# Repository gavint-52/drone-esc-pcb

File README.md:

# Drone ESC PCB

## Overview
A custom electronic speed controller (ESC) PCB designed for brushless DC motor applications.

## Design Objectives
- Design a three-phase MOSFET power stage.
- Integrate a DRV8320 gate driver.
- Use an STM32 microcontroller for control.
- Design power distribution for a 6S LiPo battery system.

## Hardware Components
- **Microcontroller:** STM32 (exact part number to be added)
- **Gate driver:** DRV8320
- **Power MOSFETs:** TI CSD18532NQ5B
- **Design software:** KiCad

## My Contributions
- Schematic design and component selection
- Gate-driver and MOSFET circuit design
- PCB component placement and routing
- Power and ground layout considerations

## Project Status
At fabrication stage of development.  

## Images
PCB renders and schematic screenshots will be added here.

## Future Work
- Complete PCB layout and design-rule checks
- Prepare fabrication files
- Assemble and test the board# drone-esc-pcb
Custom three-phase drone ESC PCB design using KiCad, an STM32 microcontroller, and a DRV8320 gate driver.

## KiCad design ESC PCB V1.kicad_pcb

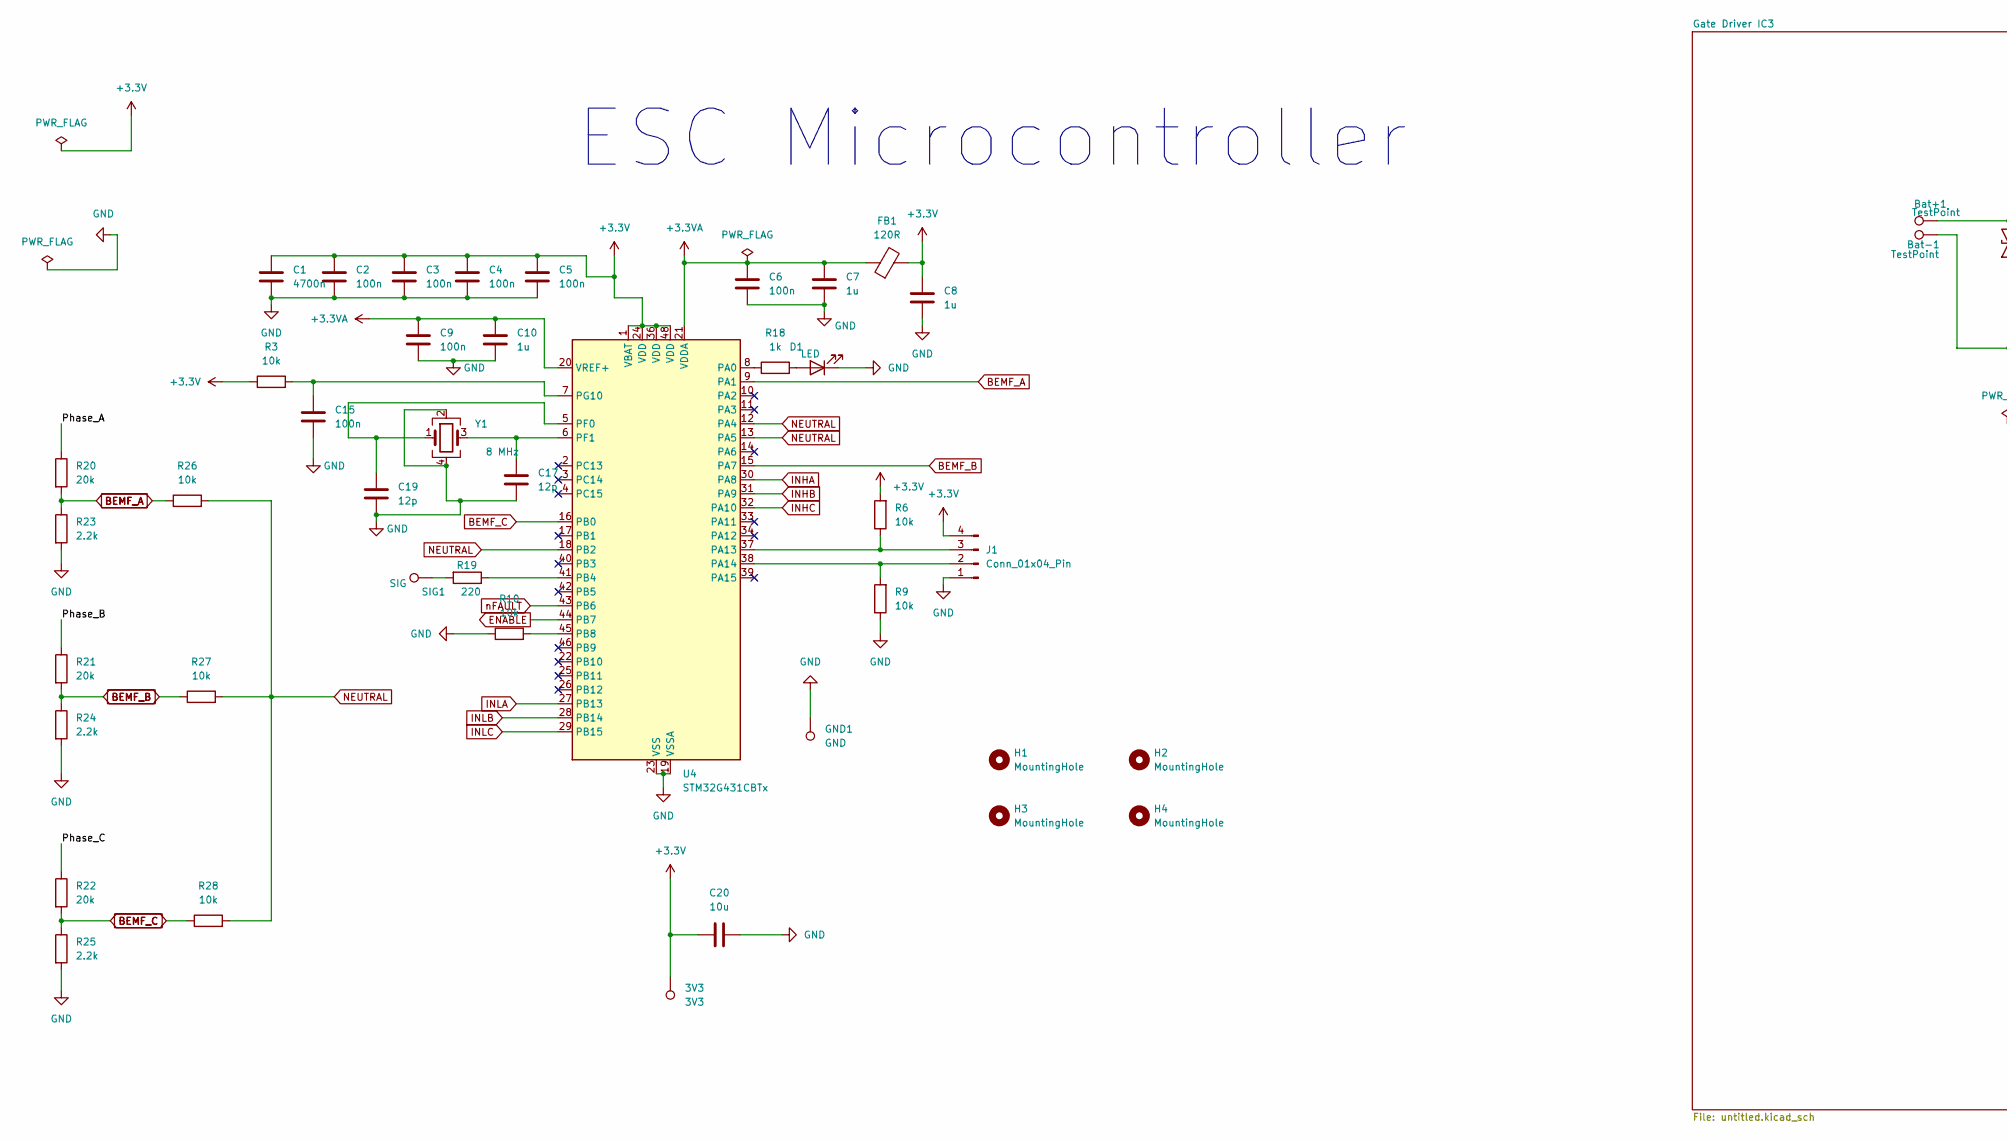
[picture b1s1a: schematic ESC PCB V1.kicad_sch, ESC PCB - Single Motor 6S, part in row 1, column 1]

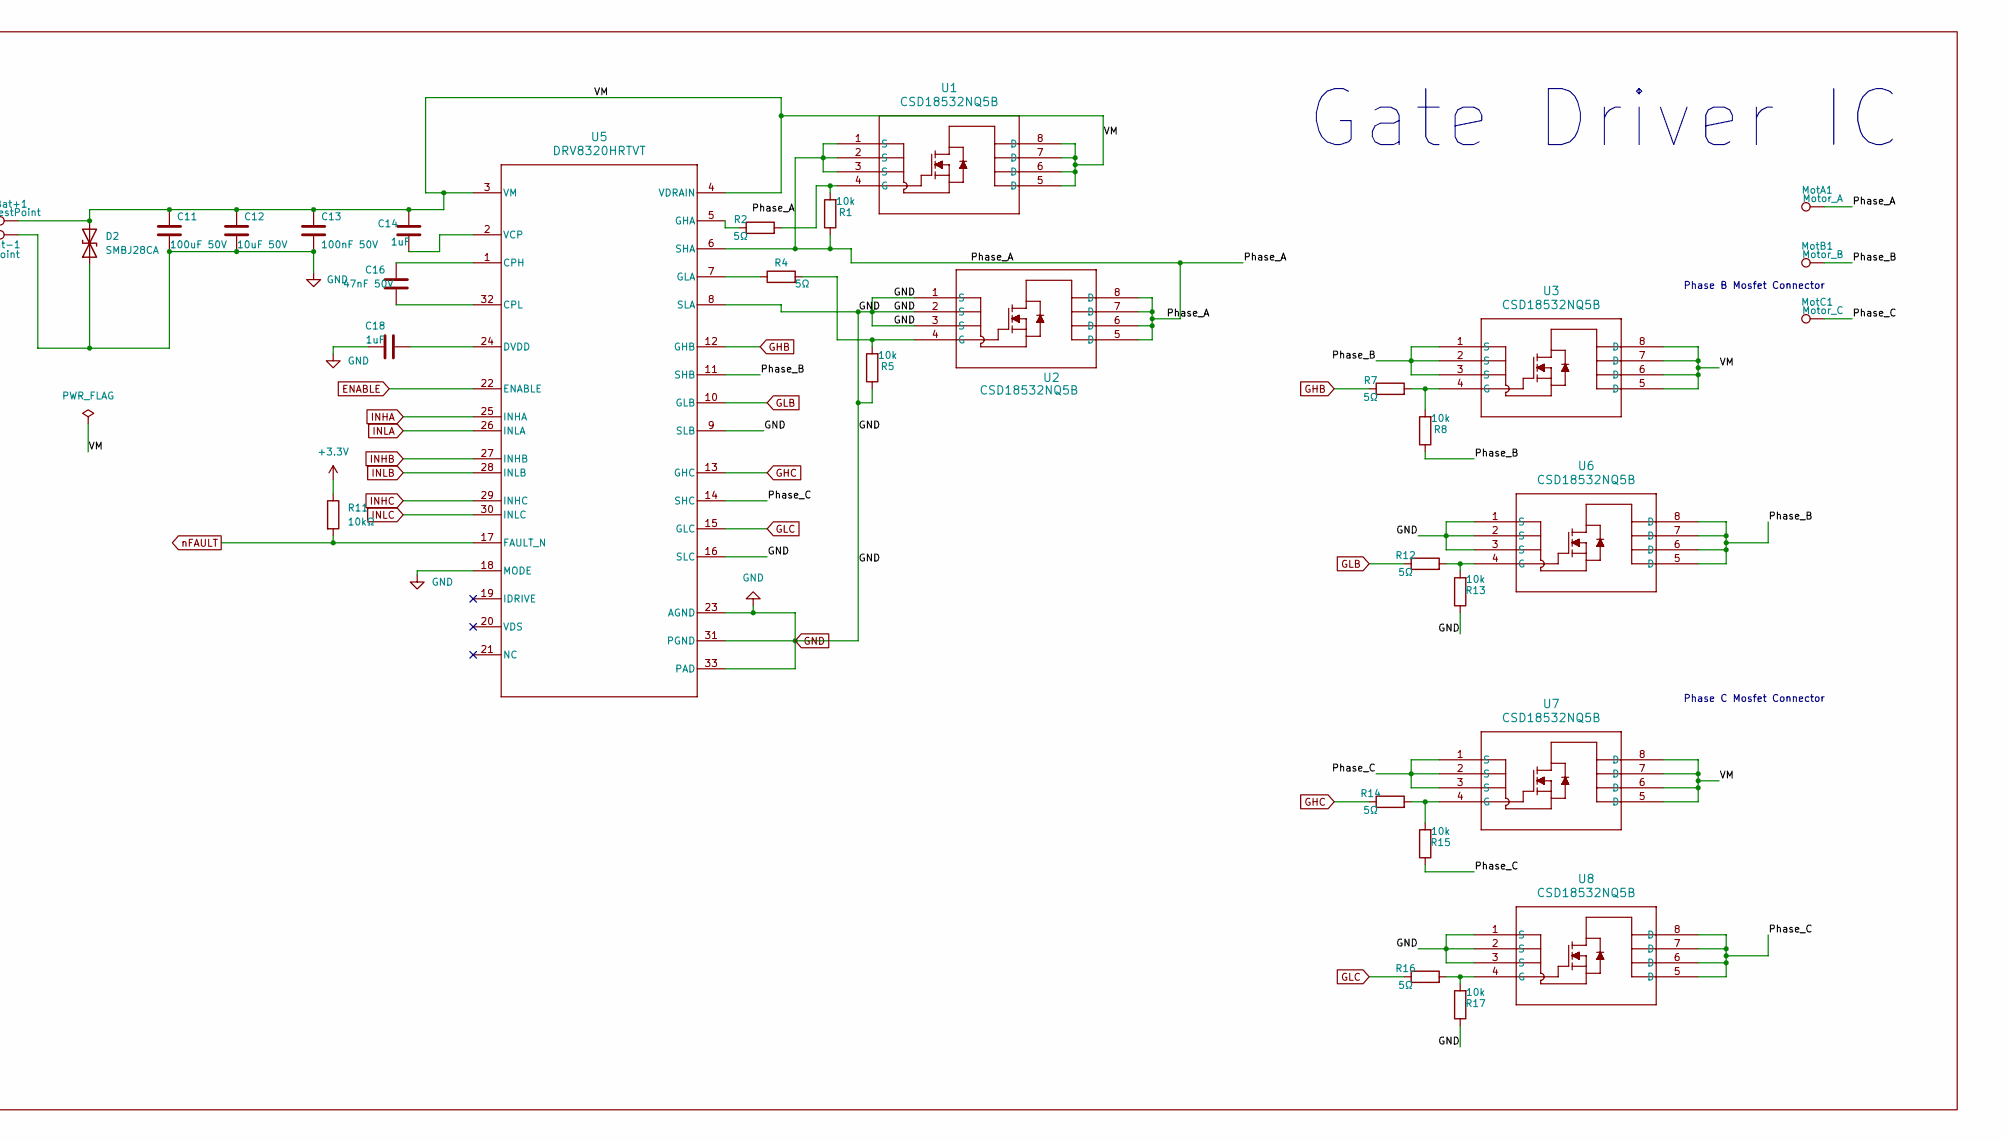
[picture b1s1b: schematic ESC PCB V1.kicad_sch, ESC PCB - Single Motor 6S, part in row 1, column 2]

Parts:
3V3: 3V3; SolderWirePad_1x01_SMD_2x4mm
Bat+1: TestPoint; SolderWirePad_1x01_SMD_5x10mm
Bat-1: TestPoint; SolderWirePad_1x01_SMD_5x10mm
C1: 4700n; C_0603_1608Metric
C2, C3, C4, C5, C6, C9, C15: 100n; C_0603_1608Metric
C7, C8, C10: 1u; C_0603_1608Metric
C11: 100uF 50V; CP_Elec_10x10.5
C12: 10uF 50V; C_1210_3225Metric
C13: 100nF 50V; C_0603_1608Metric
C14, C18: 1uF; C_0603_1608Metric
C16: 47nF 50V; C_0603_1608Metric
C17, C19: 12p; C_0603_1608Metric
C20: 10u; C_0603_1608Metric
D1: LED; LED_0603_1608Metric
D2: SMBJ28CA; SMBJSeries_LTF
FB1: 120R; L_0603_1608Metric
GND1: GND; SolderWirePad_1x01_SMD_2x4mm
H1, H2, H3, H4: MountingHole; MountingHole_3.2mm_M3
J1: Conn_01x04_Pin; PinSocket_1x04_P1.00mm_Vertical
MotA1: Motor_A; SolderWirePad_1x01_SMD_5x10mm
MotB1: Motor_B; SolderWirePad_1x01_SMD_5x10mm
MotC1: Motor_C; SolderWirePad_1x01_SMD_5x10mm
R1, R5, R8, R13, R15, R17: 10k; R_0805_2012Metric
R2, R4, R7, R12, R14, R16: 5Ω; R_0805_2012Metric
R3, R6, R9, R10, R26, R27, R28: 10k; R_0603_1608Metric
R11: 10kΩ; R_0603_1608Metric
R18: 1k; R_0603_1608Metric
R19: 220; R_0603_1608Metric
R20, R21, R22: 20k; R_0603_1608Metric
R23, R24, R25: 2.2k; R_0603_1608Metric
SIG1: SIG; SolderWirePad_1x01_SMD_2x4mm
U1, U2, U3, U6, U7, U8: CSD18532NQ5B; DNK8_TEX
U4: STM32G431CBTx; LQFP-48_7x7mm_P0.5mm
U5: DRV8320HRTVT; RTV0032E
Y1: 8 MHz; Crystal_SMD_3225-4Pin_3.2x2.5mm

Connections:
+3.3V: 3V3.1, C1.1, C2.1, C3.1, C4.1, C5.1, C8.1, C20.1, FB1.2, J1.4, R3.1, R6.2, R11.1, U4.1 (VBAT), U4.24 (VDD), U4.36 (VDD), U4.48 (VDD)
+3.3VA: C6.1, C7.1, C9.1, C10.1, FB1.1, U4.20 (VREF+), U4.21 (VDDA)
/Phase_A: MotA1.1, R1.1, R20.1, U1.1 (S), U1.2 (S), U1.3 (S), U2.5 (D), U2.6 (D), U2.7 (D), U2.8 (D), U5.6 (SHA)
/Phase_B: MotB1.1, R8.1, R21.1, U3.1 (S), U3.2 (S), U3.3 (S), U5.11 (SHB), U6.5 (D), U6.6 (D), U6.7 (D), U6.8 (D)
/Phase_C: MotC1.1, R15.1, R22.1, U5.14 (SHC), U7.1 (S), U7.2 (S), U7.3 (S), U8.5 (D), U8.6 (D), U8.7 (D), U8.8 (D)
/VM: Bat+1.1, C11.1, C12.1, C13.1, C14.2, D2.2 (A2), U1.5 (D), U1.6 (D), U1.7 (D), U1.8 (D), U3.5 (D), U3.6 (D), U3.7 (D), U3.8 (D), U5.3 (VM), U5.4 (VDRAIN), U7.5 (D), U7.6 (D), U7.7 (D), U7.8 (D)
BEMF_A: R20.2, R23.1, R26.1, U4.9 (PA1)
BEMF_B: R21.2, R24.1, R27.1, U4.15 (PA7)
BEMF_C: R22.2, R25.1, R28.1, U4.16 (PB0)
ENABLE: U4.44 (PB7), U5.22 (ENABLE)
GHB: R7.1, U5.12 (GHB)
GHC: R14.1, U5.13 (GHC)
GLB: R12.1, U5.10 (GLB)
GLC: R16.1, U5.15 (GLC)
GND: Bat-1.1, C1.2, C2.2, C3.2, C4.2, C5.2, C6.2, C7.2, C8.2, C9.2, C10.2, C11.2, C12.2, C13.2, C15.2, C17.2, C18.1, C19.2, C20.2, D1.1 (K), D2.1 (A1), GND1.1, J1.1, R5.1, R9.1, R10.1, R13.1, R17.1, R23.2, R24.2, R25.2, U2.1 (S), U2.2 (S), U2.3 (S), U4.19 (VSSA), U4.23 (VSS), U4.35 (VSS), U4.47 (VSS), U5.8 (SLA), U5.9 (SLB), U5.16 (SLC), U5.18 (MODE), U5.23 (AGND), U5.31 (PGND), U5.33 (PAD), U6.1 (S), U6.2 (S), U6.3 (S), U8.1 (S), U8.2 (S), U8.3 (S), Y1.2, Y1.4
INHA: U4.30 (PA8), U5.25 (INHA)
INHB: U4.31 (PA9), U5.27 (INHB)
INHC: U4.32 (PA10), U5.29 (INHC)
INLA: U4.27 (PB13), U5.26 (INLA)
INLB: U4.28 (PB14), U5.28 (INLB)
INLC: U4.29 (PB15), U5.30 (INLC)
NEUTRAL: R26.2, R27.2, R28.2, U4.12 (PA4), U4.13 (PA5), U4.18 (PB2)
unnamed: D1.2 (A), R18.2
unnamed: J1.2, R9.2, U4.38 (PA14)
unnamed: J1.3, R6.1, U4.37 (PA13)
unnamed: R19.2, SIG1.1
unnamed: R1.2, R2.2, U1.4 (G)
unnamed: R4.2, R5.2, U2.4 (G)
unnamed: R7.2, R8.2, U3.4 (G)
unnamed: R18.1, U4.8 (PA0)
unnamed: R19.1, U4.41 (PB4)
unnamed: R10.2, U4.45 (PB8)
unnamed: C19.1, U4.5 (PF0), Y1.1
unnamed: C17.1, U4.6 (PF1), Y1.3
unnamed: C15.1, R3.2, U4.7 (PG10)
unnamed: C16.2, U5.1 (CPH)
unnamed: C16.1, U5.32 (CPL)
unnamed: C18.2, U5.24 (DVDD)
unnamed: R2.1, U5.5 (GHA)
unnamed: R4.1, U5.7 (GLA)
unnamed: C14.1, U5.2 (VCP)
unnamed: R12.2, R13.2, U6.4 (G)
unnamed: R14.2, R15.2, U7.4 (G)
unnamed: R16.2, R17.2, U8.4 (G)
nFAULT: R11.2, U4.43 (PB6), U5.17 (FAULT_N)

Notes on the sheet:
Phase C Mosfet Connector
Phase B Mosfet Connector
Gate Driver IC
ESC Microcontroller

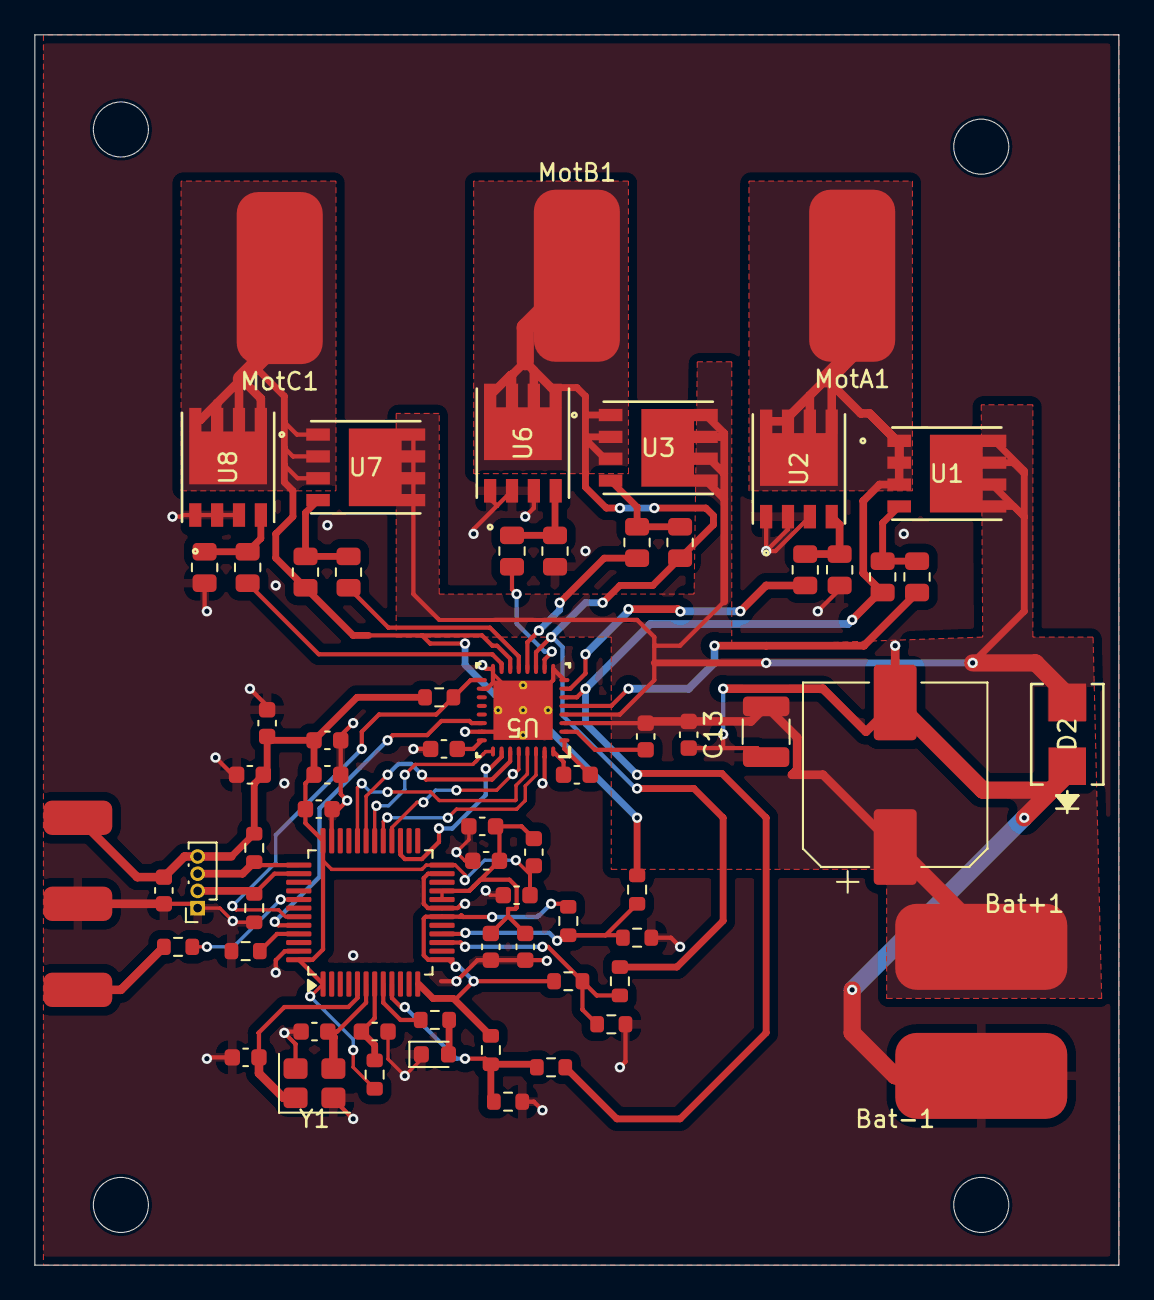
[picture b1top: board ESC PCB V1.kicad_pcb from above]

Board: 2 copper layers, 63.0 x 71.5 mm, 73 parts (0 on the bottom side), 45 nets.
